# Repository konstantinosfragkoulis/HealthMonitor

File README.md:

# HealthMonitor 

Bare metal wearable for real-time Electrocardiogram (ECG), Seismocardiogram (SCG), and respiratory rate extraction.

**Core Stack:** STM32U5 (Cortex-M33) | ST1VAFE6AX (6-axis IMU) | AD8232 (ECG AFE)

## Architecture & DSP
To guarantee precise timing, the firmware relies entirely on hardware synchronization. The IMU's data-ready external interrupt triggers a simultaneous DMA transfer for both the SPI bus (IMU) and the ADC (ECG). This locks both data streams to a 480 Hz sample rate, eliminating software polling jitter.

The main loop runs three independent DSP pipelines on-device:

* **ECG (Pan-Tompkins++):** Bandpass -> derivative -> squaring -> flattop smoothing -> MWI. Uses adaptive thresholding with search-back for real-time R-peak detection [1].
* **SCG (Template Matching NCC):** Accel Z-axis (dorso-ventral) filtered at 7-30 Hz. Bootstraps a heartbeat template during the first 10s via a 4th-power envelope and pairwise NCC [2]. Runs a sliding normalized cross-correlation against the template for continuous AO detection. The template is double-buffered and refreshed every 60s.
* **Respiratory Rate:** Accel Z-axis LPF -> decimated 48:1 (to 10 Hz) -> bandpass 0.1-0.6 Hz. Fed into a 30-second autocorrelation window, outputting a new respiratory rate every 5 seconds.

HRV metrics (RMSSD, SDNN, pNN50, SD1, SD2) are calculated independently for both the ECG and SCG streams over a 60 second sliding window based on Task Force standards [3,4]. ECG and SCG reports are synchronized as the ECG trigger drives both computations simultaneously. Data is streamed to a host via a USB Virtual COM Port with CRC-32 integrity.

## Project Structure
* `/hardware/HM-Rev1`: First spin. **See `ERRATA.md`** (known routing/schematic flaw with the AD8232).
* `/hardware/HM-Rev2`: Fixed AD8232 layout, added USB-C, placed components on the bottom layer.
* `/fw`: STM32CubeIDE project, bare-metal C source, DSP logic, and TinyUSB stack.
* `/software`: Python telemetry parser and plotter.

## Roadmap
- [x] Hardware validation.
- [x] Synchronized IMU + ECG DMA capture.
- [x] ECG R-peak detection (Pan-Tompkins++).
- [x] SCG heartbeat detection (Template Matching NCC).
- [x] Real-time respiratory rate from chest-wall accelerometry.
- [x] On-device HRV metrics calculation.
- [x] USB CDC telemetry via TinyUSB.
- [x] SCG vs ECG HRV validation.
- [ ] Improve SCG RMSSD agreement
- [ ] Multi-axis respiratory fusion (PCA + gyro).

## SCG vs ECG HRV Validation

To validate the SCG pipeline, both streams are recorded simultaneously and HRV metrics are compared using Bland-Altman analysis, Pearson correlation, and ICC(2,1). Results from a 30 minute resting session (single subject, n=57 paired reports after 4 outliers removed via 3xIQR on RMSSD):

| Metric | Bias | 95% LOA | r | ICC(2,1) |
|--------|------|---------|---|----------|
| SDNN | -2.0 ms | [-6.0, +1.9] | 0.988 | 0.961 |
| SD2 | -0.9 ms | [-3.6, +1.9] | 0.996 | 0.994 |
| RMSSD | -6.3 ms | [-16.2, +3.5] | 0.378 | 0.175 |

SDNN and SD2 show excellent agreement. RMSSD underestimates ECG systematically. The SCG pipeline captures long term variability accurately but doesn't perform well with beat-to-beat variations.

The validation script reports both unfiltered and filtered results.
Run `python software/analyze.py <session_dir>` to produce the table and plots with data saved from the `software/monitor.py` script.

## Build Instructions
Compiled with **STM32CubeIDE**.
1. `git clone https://github.com/konstantinosfragkoulis/HealthMonitor.git`
2. Open STM32CubeIDE > `File > STM32 Project Create/Import > Import STM32 Project > STM32CubeMX/STM32CubeIDE Project`.
3. Point to the `/fw` directory.
4. Build (Release/Debug) and flash via ST-Link.

## Host Telemetry
The STM32 streams binary packets over USB CDC. Use the included Python script to plot sensor data in real time.

```bash
cd software
pip install pyserial numpy matplotlib # You might want to use a virtual environment for this

# Auto detect port
python monitor.py

# Manually select port
python monitor.py COM3         # Windows
python monitor.py /dev/ttyACM0 # Linux
```

## References
- USB stack powered by the open-source [TinyUSB](https://github.com/hathach/tinyusb) library (MIT License).

[1] M. N. Imtiaz and N. Khan, "Pan-Tompkins++: A Robust Approach to Detect R-peaks in ECG Signals," in *Proc. IEEE Int. Conf. Bioinformatics and Biomedicine (BIBM) Workshops*, 2022. [Online]. Available: https://arxiv.org/abs/2211.03171

[2] S. Parlato, J. Centracchio, D. Esposito, P. Bifulco, and E. Andreozzi, "Fully automated template matching method for ECG-free heartbeat detection in cardiomechanical signals," *Physical and Engineering Sciences in Medicine*, vol. 48, pp. 649-664, 2025.

[3] Task Force of the European Society of Cardiology and the North American Society of Pacing and Electrophysiology, "Heart rate variability: standards of measurement, physiological interpretation and clinical use," *Circulation*, vol. 93, pp. 1043-1065, 1996.

[4] F. Shaffer and J. P. Ginsberg, "An Overview of Heart Rate Variability Metrics and Norms," *Frontiers in Public Health*, vol. 5, 258, 2017.

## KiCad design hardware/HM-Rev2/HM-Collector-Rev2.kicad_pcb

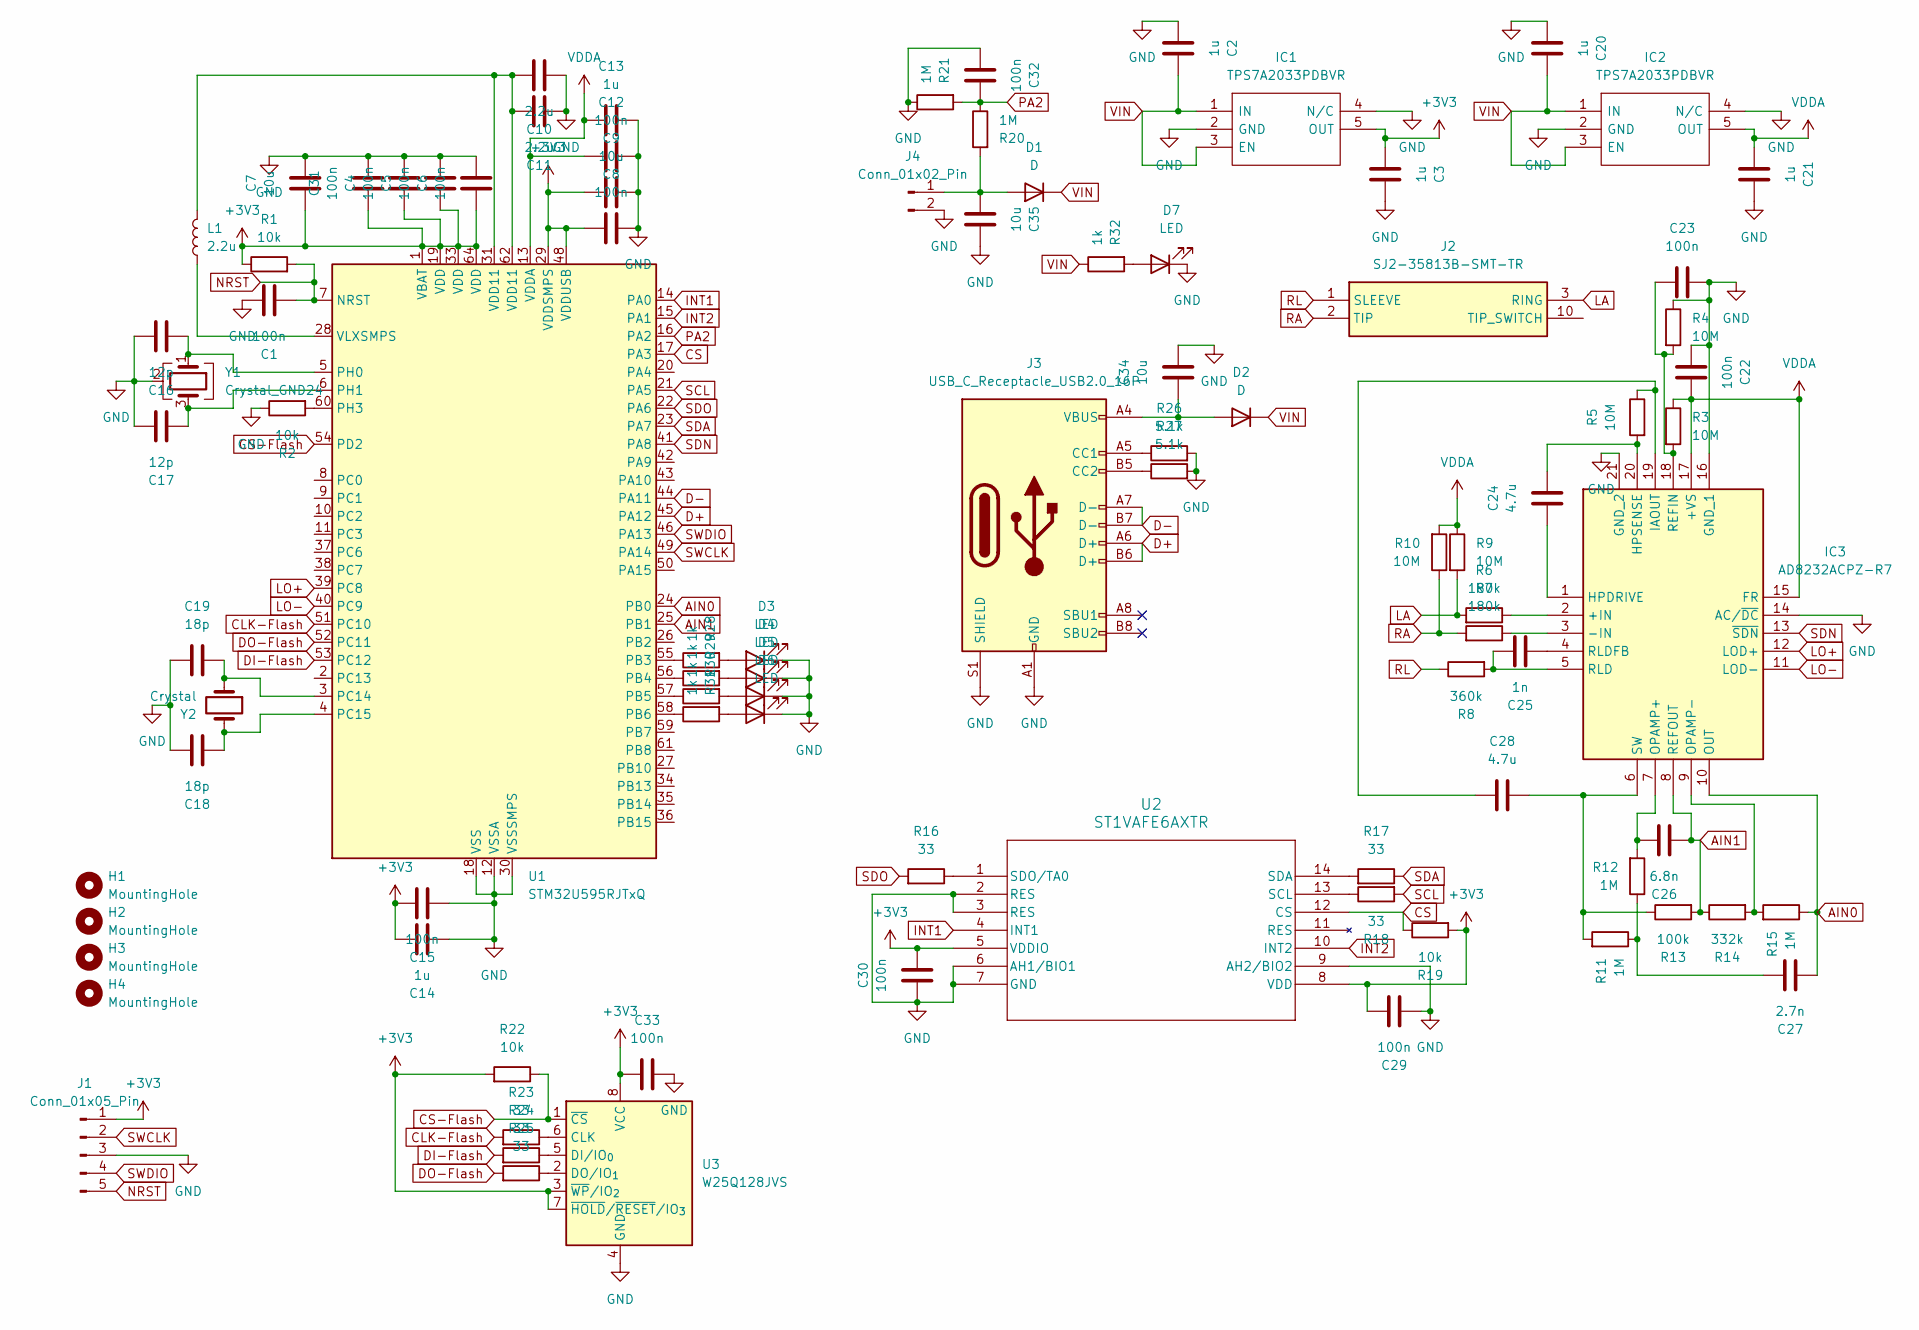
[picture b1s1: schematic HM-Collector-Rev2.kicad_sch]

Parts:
C1, C4, C5, C6, C8, C12, C15, C22, C23, C29, C30, C31, C32, C33: 100n; C_0603_1608Metric
C2, C3, C13, C14, C20, C21: 1u; C_0603_1608Metric
C7, C9, C34, C35: 10u; C_0805_2012Metric
C10, C11: 2.2u; C_0603_1608Metric
C16, C17: 12p; C_0402_1005Metric
C18, C19: 18p; C_0402_1005Metric
C24, C28: 4.7u; C_0805_2012Metric
C25: 1n; C_0603_1608Metric
C26: 6.8n; C_0402_1005Metric
C27: 2.7n; C_0603_1608Metric
D1, D2: D; D_SOD-123
D3, D4, D5, D6, D7: LED; LED_0603_1608Metric
H1, H2, H3, H4: MountingHole; MountingHole_2.2mm_M2
IC1, IC2: TPS7A2033PDBVR; SOT95P280X145-5N; Manufacturer_Part_Number TPS7A2033PDBVR; Mouser Part Number 595-TPS7A2033PDBVR
IC3: AD8232ACPZ-R7; QFN50P400X400X80-21N-D; Mouser Part Number 584-AD8232ACPZ-R7
J1: Conn_01x05_Pin; PinHeader_1x05_P2.54mm_Horizontal
J2: SJ2-35813B-SMT-TR; SJ235813BSMTTR; Mouser Part Number 490-SJ2-35813BSMT-TR
J3: USB_C_Receptacle_USB2.0_16P; USB_C_Receptacle_GCT_USB4105-xx-A_16P_TopMnt_Horizontal
J4: Conn_01x02_Pin; PinHeader_1x02_P2.54mm_Vertical
L1: 2.2u; L_1008_2520Metric
R1, R2, R19, R22: 10k; R_0603_1608Metric
R3, R4, R5, R9, R10: 10M; R_0603_1608Metric
R6, R7: 180k; R_0603_1608Metric
R8: 360k; R_0603_1608Metric
R11, R12, R15, R20, R21: 1M; R_0603_1608Metric
R13: 100k; R_0603_1608Metric
R14: 332k; R_0603_1608Metric
R16, R17, R18, R23, R24, R25: 33; R_0603_1608Metric
R26, R27: 5.1k; R_0603_1608Metric
R28, R29, R30, R31, R32: 1k; R_0603_1608Metric
U1: STM32U595RJTxQ; LQFP-64_10x10mm_P0.5mm
U2: ST1VAFE6AXTR; LGA-14L_STM
U3: W25Q128JVS; SOIC-8_5.3x5.3mm_P1.27mm
Y1: Crystal_GND24; Crystal_SMD_3225-4Pin_3.2x2.5mm
Y2: Crystal; Crystal_SMD_3215-2Pin_3.2x1.5mm

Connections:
+3V3: C3.2, C4.2, C5.2, C6.2, C7.2, C8.2, C9.2, C14.2, C15.1, C29.1, C30.1, C31.2, C33.2, IC1.5 (OUT), J1.1, R1.1, R19.2, R22.2, U1.1 (VBAT), U1.19 (VDD), U1.29 (VDDSMPS), U1.33 (VDD), U1.48 (VDDUSB), U1.64 (VDD), U2.5 (VDDIO), U2.8 (VDD), U3.3 (~WP/IO_{2}), U3.7 (~HOLD/~RESET/IO_{3}), U3.8 (VCC)
AIN0: C27.2, IC3.10 (OUT), R15.1, U1.24 (PB0)
AIN1: C26.2, IC3.8 (REFOUT), R13.2, R14.1, U1.25 (PB1)
CLK-Flash: R23.2, U1.51 (PC10)
CS: R19.1, U1.17 (PA3), U2.12 (CS)
CS-Flash: R22.1, U1.54 (PD2), U3.1 (~CS)
D+: J3.A6 (D+), J3.B6 (D+), U1.45 (PA12)
D-: J3.A7 (D-), J3.B7 (D-), U1.44 (PA11)
DI-Flash: R24.2, U1.53 (PC12)
DO-Flash: R25.2, U1.52 (PC11)
GND: C1.1, C2.2, C3.1, C4.1, C5.1, C6.1, C7.1, C8.1, C9.1, C10.1, C11.1, C12.1, C13.2, C14.1, C15.2, C16.1, C17.1, C18.1, C19.2, C20.2, C21.1, C22.2, C23.1, C29.2, C30.2, C31.1, C32.2, C33.1, C34.1, C35.1, D3.1 (K), D4.1 (K), D5.1 (K), D6.1 (K), D7.1 (K), IC1.2 (GND), IC1.4 (N/C), IC2.2 (GND), IC2.4 (N/C), IC3.14 (AC/~DC), IC3.16 (GND_1), IC3.21 (GND_2), J1.3, J3.A1 (GND), J3.A12 (GND), J3.B1 (GND), J3.B12 (GND), J3.S1 (SHIELD), J4.2, R2.1, R4.1, R21.1, R26.2, R27.2, U1.12 (VSSA), U1.18 (VSS), U1.30 (VSSSMPS), U1.32 (VSS), U1.47 (VSS), U1.63 (VSS), U2.2 (RES), U2.3 (RES), U2.6 (AH1/BIO1), U2.7 (GND), U2.9 (AH2/BIO2), U3.4 (GND), Y1.2 (G), Y1.4 (G)
INT1: U1.14 (PA0), U2.4 (INT1)
INT2: U1.15 (PA1), U2.10 (INT2)
LA: J2.3 (RING), R6.2, R9.2
LO+: IC3.12 (LOD+), U1.39 (PC8)
LO-: IC3.11 (LOD-), U1.40 (PC9)
NRST: C1.2, J1.5, R1.2, U1.7 (NRST)
unnamed: C10.2, C11.2, L1.2, U1.31 (VDD11), U1.62 (VDD11)
unnamed: C27.1, R11.1, R12.1
unnamed: C35.2, D1.2 (A), J4.1, R20.2
unnamed: C34.2, D2.2 (A), J3.A4 (VBUS), J3.A9 (VBUS), J3.B4 (VBUS), J3.B9 (VBUS)
unnamed: D3.2 (A), R28.2
unnamed: D4.2 (A), R29.2
unnamed: D5.2 (A), R30.2
unnamed: D6.2 (A), R31.2
unnamed: D7.2 (A), R32.2
unnamed: IC3.2 (+IN), R6.1
unnamed: IC3.3 (-IN), R7.1
unnamed: C24.2, IC3.1 (HPDRIVE)
unnamed: C24.1, IC3.20 (HPSENSE), R5.2
unnamed: C28.2, IC3.19 (IAOUT), R5.1
unnamed: C26.1, IC3.7 (OPAMP+), R12.2
unnamed: IC3.9 (OPAMP-), R14.2, R15.2
unnamed: C23.2, IC3.18 (REFIN), R3.2, R4.2
unnamed: C25.1, IC3.5 (RLD), R8.2
unnamed: C25.2, IC3.4 (RLDFB)
unnamed: C28.1, IC3.6 (SW), R11.2, R13.1
unnamed: J3.A5 (CC1), R26.1
unnamed: J3.B5 (CC2), R27.1
unnamed: R28.1, U1.55 (PB3)
unnamed: R29.1, U1.56 (PB4)
unnamed: R30.1, U1.57 (PB5)
unnamed: R31.1, U1.58 (PB6)
unnamed: C19.1, U1.3 (PC14), Y2.1
unnamed: C18.2, U1.4 (PC15), Y2.2
unnamed: C16.2, U1.5 (PH0), Y1.1
unnamed: C17.2, U1.6 (PH1), Y1.3
unnamed: R2.2, U1.60 (PH3)
unnamed: L1.1, U1.28 (VLXSMPS)
unnamed: R18.1, U2.13 (SCL)
unnamed: R17.2, U2.14 (SDA)
unnamed: R16.1, U2.1 (SDO/TA0)
unnamed: R23.1, U3.6 (CLK)
unnamed: R24.1, U3.5 (DI/IO_{0})
unnamed: R25.1, U3.2 (DO/IO_{1})
PA2: C32.1, R20.1, R21.2, U1.16 (PA2)
RA: J2.2 (TIP), R7.2, R10.1
RL: J2.1 (SLEEVE), R8.1
SCL: R18.2, U1.21 (PA5)
SDA: R17.1, U1.23 (PA7)
SDN: IC3.13 (~SDN), U1.41 (PA8)
SDO: R16.2, U1.22 (PA6)
SWCLK: J1.2, U1.49 (PA14)
SWDIO: J1.4, U1.46 (PA13)
VDDA: C12.2, C13.1, C21.2, C22.1, IC2.5 (OUT), IC3.15 (FR), IC3.17 (+VS), R3.1, R9.1, R10.2, U1.13 (VDDA)
VIN: C2.1, C20.1, D1.1 (K), D2.1 (K), IC1.1 (IN), IC1.3 (EN), IC2.1 (IN), IC2.3 (EN), R32.1

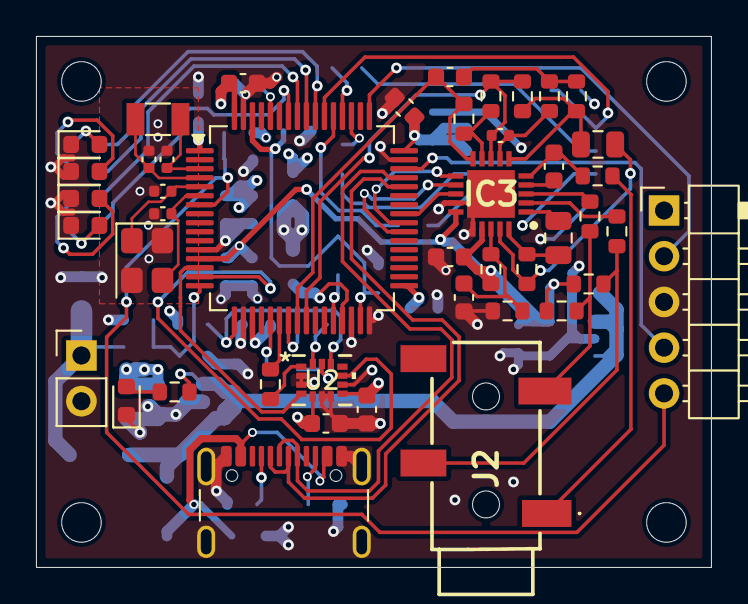
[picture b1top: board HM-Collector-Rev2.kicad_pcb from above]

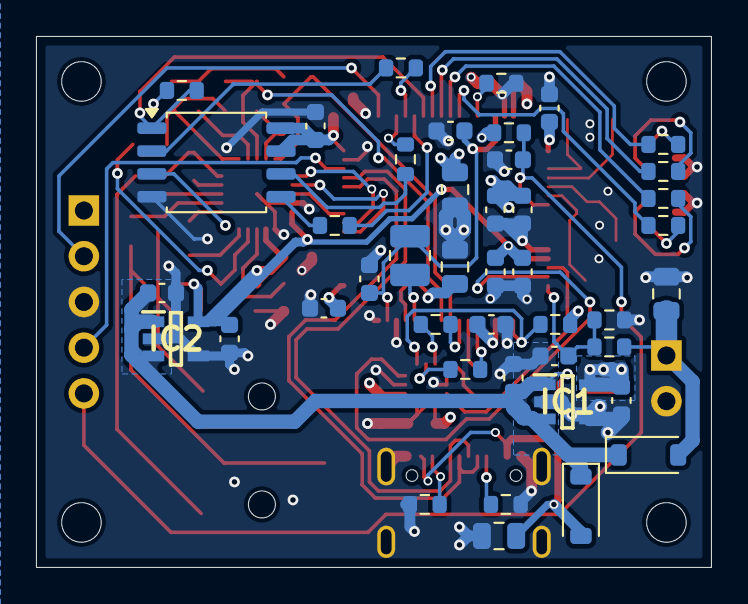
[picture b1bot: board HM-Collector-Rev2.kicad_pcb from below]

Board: 4 copper layers, 37.5 x 29.5 mm, 91 parts (43 on the bottom side), 66 nets.

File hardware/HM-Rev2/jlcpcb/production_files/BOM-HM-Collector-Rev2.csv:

Comment,Designator,Footprint,LCSC,Quantity
100k,R13,R_0603_1608Metric,C25803,1
100n,"C1,C12,C15,C22,C23,C29,C30,C31,C32,C33,C4,C5,C6,C8",C_0603_1608Metric,C14663,14
10M,"R10,R3,R4,R5,R9",R_0603_1608Metric,C7250,5
10k,"R1,R19,R2,R22",R_0603_1608Metric,C25804,4
10u,"C34,C35,C7,C9",C_0805_2012Metric,C440198,4
12p,"C16,C17",C_0402_1005Metric,C1547,2
180k,"R6,R7",R_0603_1608Metric,C22827,2
18p,"C18,C19",C_0402_1005Metric,C1549,2
1M,"R11,R12,R15,R20,R21",R_0603_1608Metric,C22935,5
1k,"R28,R29,R30,R31,R32",R_0603_1608Metric,C21190,5
1n,C25,C_0603_1608Metric,C1588,1
1u,"C13,C14,C2,C20,C21,C3",C_0603_1608Metric,C15849,6
2.2u,"C10,C11",C_0603_1608Metric,C23630,2
2.7n,C27,C_0603_1608Metric,C1609,1
33,"R16,R17,R18,R23,R24,R25",R_0603_1608Metric,C23140,6
4.7u,"C24,C28",C_0805_2012Metric,C1779,2
5.1k,"R26,R27",R_0603_1608Metric,C23186,2
6.8n,C26,C_0402_1005Metric,C1542,1
AD8232ACPZ-R7,IC2,QFN50P400X400X80-21N-D,C43216,1
Crystal,Y2,Crystal_SMD_3215-2Pin_3.2x1.5mm,C32346,1
Crystal_GND24,Y1,Crystal_SMD_3225-4Pin_3.2x2.5mm,C13738,1
D,"D1,D2",D_SOD-123,C8598,2
LED,"D3,D5,D7",LED_0603_1608Metric,C2286,3
LED,"D4,D6",LED_0603_1608Metric,C2290,2
ST1VAFE6AXTR,U2,LGA-14L_STM,C23536654,1
STM32U595RJTxQ,U1,LQFP-64_10x10mm_P0.5mm,C27526235,1
TPS7A2028PDBVR,"IC1,IC3",SOT95P280X145-5N,C2862740,2
USB_C_Receptacle_USB2.0_16P,J3,USB_C_Receptacle_GCT_USB4105-xx-A_16P_TopMnt_Horizontal,C709357,1

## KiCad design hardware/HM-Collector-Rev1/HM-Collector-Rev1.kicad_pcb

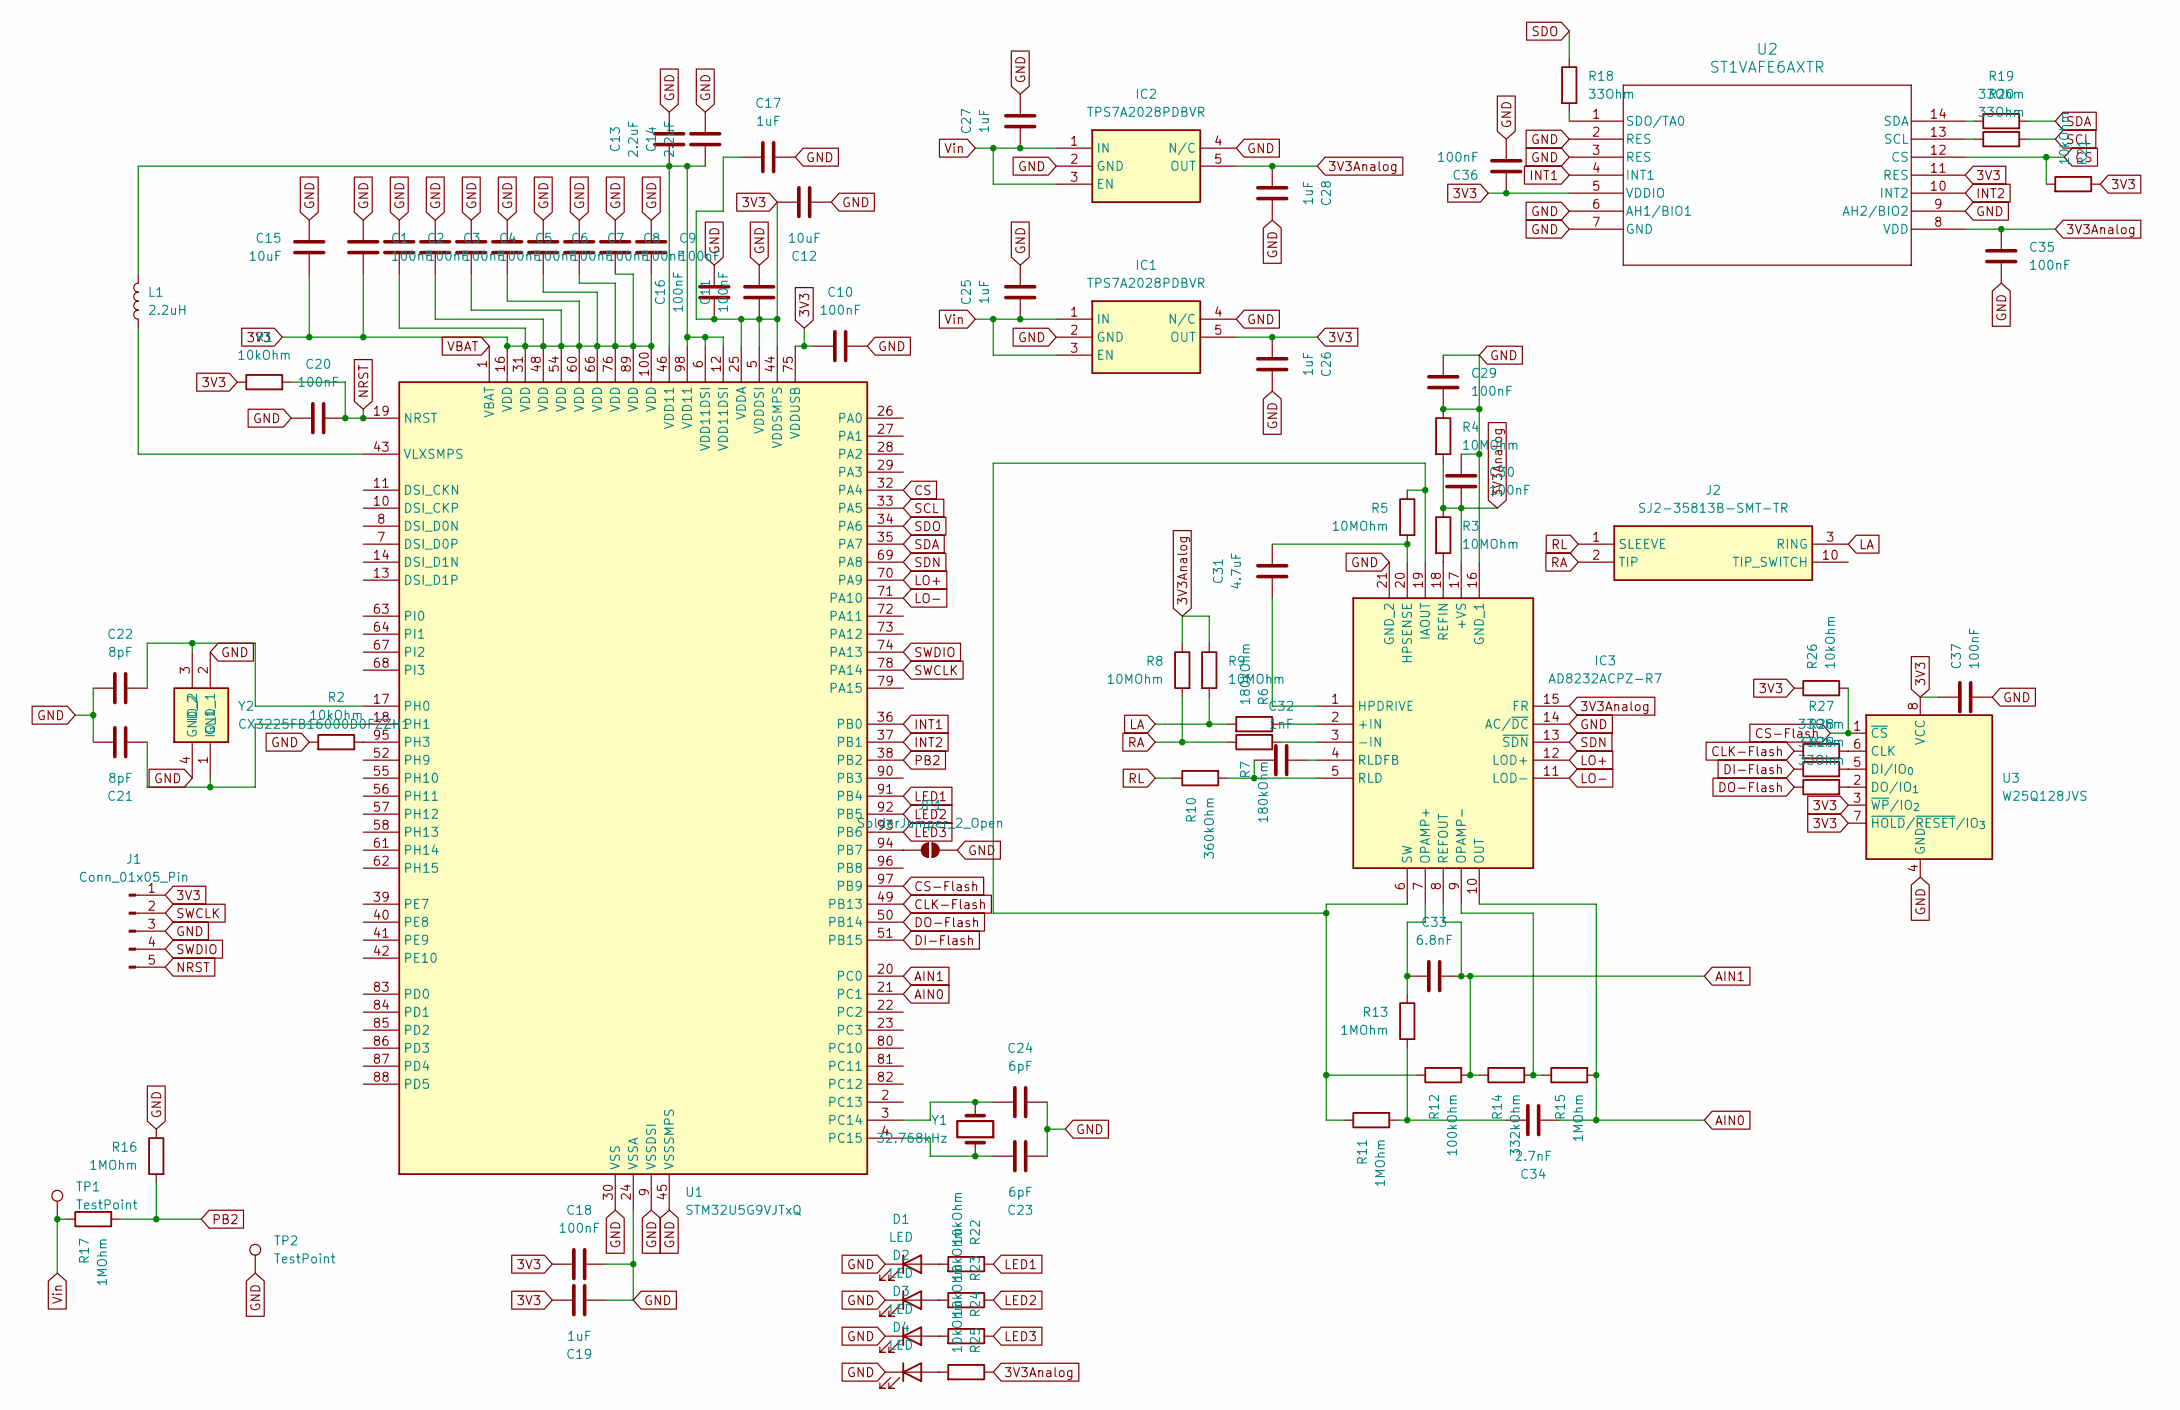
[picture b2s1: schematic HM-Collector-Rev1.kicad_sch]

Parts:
C1, C2, C3, C4, C5, C6, C7, C8, C9, C10, C11, C16, C18, C20, C29, C30, C35, C36, C37: 100nF; C_0603_1608Metric
C12, C15: 10uF; C_0805_2012Metric
C13, C14: 2.2uF; C_0603_1608Metric
C17, C19, C25, C26, C27, C28: 1uF; C_0603_1608Metric
C21, C22: 8pF; C_0402_1005Metric
C23, C24: 6pF; C_0402_1005Metric
C31: 4.7uF; C_0805_2012Metric
C32: 1nF; C_0603_1608Metric
C33: 6.8nF; C_0402_1005Metric
C34: 2.7nF; C_0402_1005Metric
D1, D2, D3, D4: LED; LED_0402_1005Metric_Pad0.77x0.64mm_HandSolder
IC1, IC2: TPS7A2028PDBVR; SOT95P280X145-5N; Mouser Part Number 595-TPS7A2028PDBVR
IC3: AD8232ACPZ-R7; QFN50P400X400X80-21N-D; Mouser Part Number 584-AD8232ACPZ-R7
J1: Conn_01x05_Pin; PinHeader_1x05_P2.54mm_Horizontal
J2: SJ2-35813B-SMT-TR; SJ235813BSMTTR; Mouser Part Number 490-SJ2-35813BSMT-TR
JP1: SolderJumper_2_Open; SolderJumper-2_P1.3mm_Open_Pad1.0x1.5mm
L1: 2.2uH; L_1008_2520Metric
R1, R2, R21, R22, R23, R24, R25, R26: 10kOhm; R_0603_1608Metric
R3, R4, R5, R8, R9: 10MOhm; R_0603_1608Metric
R6, R7: 180kOhm; R_0603_1608Metric
R10: 360kOhm; R_0603_1608Metric
R11, R13, R15, R16, R17: 1MOhm; R_0603_1608Metric
R12: 100kOhm; R_0603_1608Metric
R14: 332kOhm; R_0603_1608Metric
R18, R19, R20, R27, R28, R29: 33Ohm; R_0402_1005Metric
TP1, TP2: TestPoint; PinHeader_1x01_P2.54mm_Vertical
U1: STM32U5G9VJTxQ; LQFP-100_14x14mm_P0.5mm
U2: ST1VAFE6AXTR; LGA-14L_STM
U3: W25Q128JVS; SOIC-8_5.3x5.3mm_P1.27mm
Y1: 32.768kHz; Crystal_SMD_3215-2Pin_3.2x1.5mm
Y2: CX3225FB16000D0FZZH1; Manufacturer_Part_Number CX3225FB16000D0FZZH1

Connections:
3V3: C1.2, C2.2, C3.2, C4.2, C5.2, C6.2, C7.2, C8.2, C9.2, C10.1, C11.1, C12.1, C15.2, C16.1, C17.1, C18.2, C19.1, C26.1, C36.1, C37.1, IC1.5 (OUT), J1.1, R1.1, R21.1, R26.1, U1.5 (VDDDSI), U1.16 (VDD), U1.25 (VDDA), U1.31 (VDD), U1.44 (VDDSMPS), U1.48 (VDD), U1.54 (VDD), U1.60 (VDD), U1.66 (VDD), U1.75 (VDDUSB), U1.76 (VDD), U1.89 (VDD), U1.100 (VDD), U2.5 (VDDIO), U2.11 (RES), U3.3 (~WP/IO_{2}), U3.7 (~HOLD/~RESET/IO_{3}), U3.8 (VCC)
3V3Analog: C28.1, C30.1, C35.1, IC2.5 (OUT), IC3.15 (FR), IC3.17 (+VS), R3.1, R4.2, R8.1, R9.1, R25.1, U2.8 (VDD)
AIN0: C34.2, IC3.10 (OUT), R15.2, U1.21 (PC1)
AIN1: C33.1, IC3.8 (REFOUT), R12.2, R14.1, U1.20 (PC0)
CLK-Flash: R27.1, U1.49 (PB13)
CS: R21.2, U1.32 (PA4), U2.12 (CS)
CS-Flash: R26.2, U1.97 (PB9), U3.1 (~CS)
DI-Flash: R28.1, U1.51 (PB15)
DO-Flash: R29.1, U1.50 (PB14)
GND: C1.1, C2.1, C3.1, C4.1, C5.1, C6.1, C7.1, C8.1, C9.1, C10.2, C11.2, C12.2, C13.2, C14.2, C15.1, C16.2, C17.2, C18.1, C19.2, C20.1, C21.1, C22.2, C23.2, C24.1, C25.2, C26.2, C27.2, C28.2, C29.1, C29.2, C30.2, C35.2, C36.2, C37.2, D1.1 (K), D2.1 (K), D3.1 (K), D4.1 (K), IC1.2 (GND), IC1.4 (N/C), IC2.2 (GND), IC2.4 (N/C), IC3.14 (AC/~DC), IC3.16 (GND_1), IC3.21 (GND_2), J1.3, JP1.2 (B), R2.2, R4.1, R16.1, TP2.1, U1.9 (VSSDSI), U1.15 (VSSDSI), U1.24 (VSSA), U1.30 (VSS), U1.45 (VSSSMPS), U1.47 (VSS), U1.53 (VSS), U1.59 (VSS), U1.65 (VSS), U1.77 (VSS), U1.99 (VSS), U2.2 (RES), U2.3 (RES), U2.6 (AH1/BIO1), U2.7 (GND), U2.9 (AH2/BIO2), U3.4 (GND), Y2.2 (GND_1), Y2.4 (GND_2)
INT1: U1.36 (PB0), U2.4 (INT1)
INT2: U1.37 (PB1), U2.10 (INT2)
LA: J2.3 (RING), R6.2, R9.2
LED1: R22.1, U1.91 (PB4)
LED2: R23.1, U1.92 (PB5)
LED3: R24.1, U1.93 (PB6)
LO+: IC3.12 (LOD+), U1.70 (PA9)
LO-: IC3.11 (LOD-), U1.71 (PA10)
NRST: C20.2, J1.5, R1.2, U1.19 (NRST)
unnamed: C13.1, C14.1, L1.2, U1.6 (VDD11DSI), U1.12 (VDD11DSI), U1.46 (VDD11), U1.98 (VDD11)
unnamed: C34.1, R11.2, R13.2
unnamed: D1.2 (A), R22.2
unnamed: D2.2 (A), R23.2
unnamed: D3.2 (A), R24.2
unnamed: D4.2 (A), R25.2
unnamed: IC3.2 (+IN), R6.1
unnamed: IC3.3 (-IN), R7.2
unnamed: C31.1, IC3.1 (HPDRIVE)
unnamed: C31.2, IC3.20 (HPSENSE), R5.2
unnamed: IC3.6 (SW), IC3.19 (IAOUT), R5.1, R11.1, R12.1
unnamed: C33.2, IC3.7 (OPAMP+), R13.1
unnamed: IC3.9 (OPAMP-), R14.2, R15.1
unnamed: IC3.18 (REFIN), R3.2
unnamed: C32.2, IC3.5 (RLD), R10.2
unnamed: C32.1, IC3.4 (RLDFB)
unnamed: JP1.1 (A), U1.94 (PB7)
unnamed: C24.2, U1.3 (PC14), Y1.2
unnamed: C23.1, U1.4 (PC15), Y1.1
unnamed: C22.1, U1.17 (PH0), Y2.3 (IO_2)
unnamed: C21.2, U1.18 (PH1), Y2.1 (IO_1)
unnamed: R2.1, U1.95 (PH3)
unnamed: L1.1, U1.43 (VLXSMPS)
unnamed: R20.1, U2.13 (SCL)
unnamed: R19.1, U2.14 (SDA)
unnamed: R18.2, U2.1 (SDO/TA0)
unnamed: R27.2, U3.6 (CLK)
unnamed: R28.2, U3.5 (DI/IO_{0})
unnamed: R29.2, U3.2 (DO/IO_{1})
PB2: R16.2, R17.2, U1.38 (PB2)
RA: J2.2 (TIP), R7.1, R8.2
RL: J2.1 (SLEEVE), R10.1
SCL: R20.2, U1.33 (PA5)
SDA: R19.2, U1.35 (PA7)
SDN: IC3.13 (~SDN), U1.69 (PA8)
SDO: R18.1, U1.34 (PA6)
SWCLK: J1.2, U1.78 (PA14)
SWDIO: J1.4, U1.74 (PA13)
VBAT: U1.1 (VBAT)
Vin: C25.1, C27.1, IC1.1 (IN), IC1.3 (EN), IC2.1 (IN), IC2.3 (EN), R17.1, TP1.1

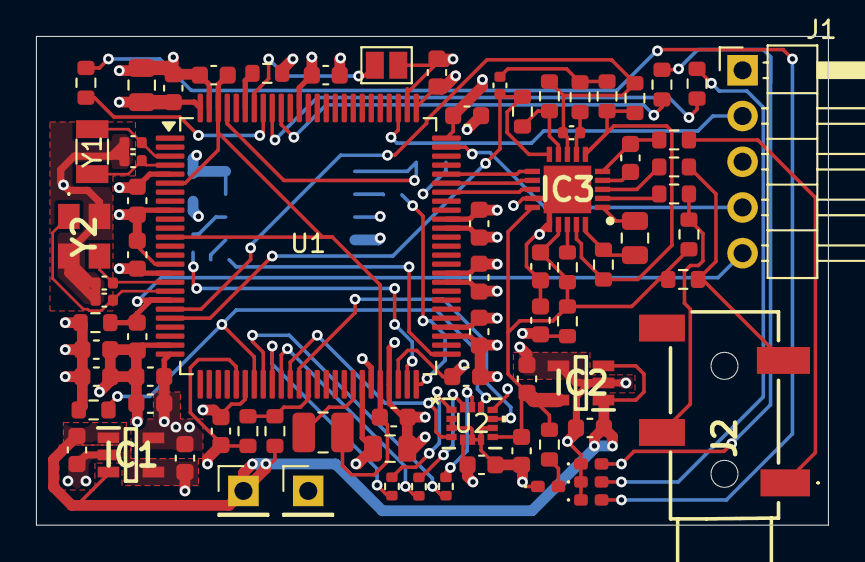
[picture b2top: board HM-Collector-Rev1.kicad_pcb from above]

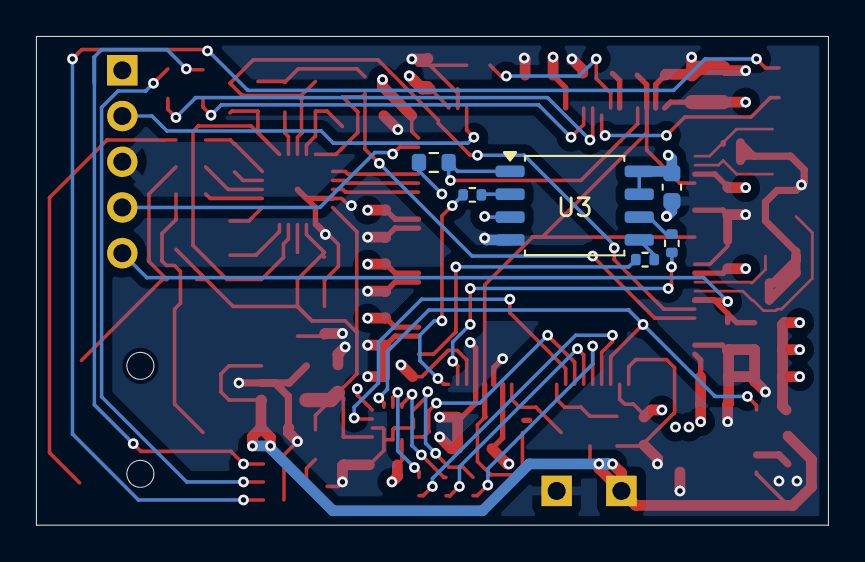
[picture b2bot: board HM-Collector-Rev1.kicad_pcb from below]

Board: 4 copper layers, 44.0 x 27.2 mm, 84 parts (6 on the bottom side), 58 nets.

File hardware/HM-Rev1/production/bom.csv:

Designator,Footprint,Quantity,Value,LCSC Part #
"C1, C10, C11, C16, C18, C2, C20, C29, C3, C30, C35, C36, C37, C4, C5, C6, C7, C8, C9",0603,19,100nF,
"C12, C15",0805,2,10uF,
"C13, C14",0603,2,2.2uF,
"C17, C19, C25, C26, C27, C28",0603,6,1uF,
"C21, C22",0402,2,8pF,
"C23, C24",0402,2,6pF,
C31,0805,1,4.7uF,
C32,0603,1,1nF,
C33,0402,1,6.8nF,
C34,0402,1,2.7nF,
"D1, D2, D3, D4",0402,4,LED,
"IC1, IC2",SOT95P280X145-5N,2,TPS7A2028PDBVR,
IC3,QFN50P400X400X80-21N-D,1,AD8232ACPZ-R7,
J1,PinHeader_1x05_P2.54mm_Horizontal,1,Conn_01x05_Pin,
J2,SJ235813BSMTTR,1,SJ2-35813B-SMT-TR,
L1,1008,1,2.2uH,
"R1, R2, R21, R22, R23, R24, R25, R26",0603,8,10kOhm,
R10,0603,1,360kOhm,
"R11, R13, R15, R16, R17",0603,5,1MOhm,
R12,0603,1,100kOhm,
R14,0603,1,332kOhm,
"R18, R19, R20, R27, R28, R29",0402,6,33Ohm,
"R3, R4, R5, R8, R9",0603,5,10MOhm,
"R6, R7",0603,2,180kOhm,
"TP1, TP2",PinHeader_1x01_P2.54mm_Vertical,2,TestPoint,
U1,LQFP-100_14x14mm_P0.5mm,1,STM32U5G9VJTxQ,
U2,LGA-14L_STM,1,ST1VAFE6AXTR,
U3,SOIC-8_5.3x5.3mm_P1.27mm,1,W25Q128JVS,
Y1,Crystal_SMD_3215-2Pin_3.2x1.5mm,1,32.768kHz,
Y2,CX3225FB16000D0FZZH1,1,CX3225FB16000D0FZZH1,

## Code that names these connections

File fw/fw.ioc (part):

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Mcu.Name=STM32U595RJTxQ
Mcu.Package=LQFP64
Mcu.UserName=STM32U595RJTxQ
PA0.GPIOParameters=GPIO_Label
PA0.GPIO_Label=IMU_INT1
PA0.Signal=GPXTI0
PA1.GPIOParameters=GPIO_Label
PA1.GPIO_Label=IMU_INT2
PA1.Signal=GPXTI1
PA11.Mode=Internal_Phy_Device
PA11.Signal=USB_OTG_HS_DM
PA12.Mode=Internal_Phy_Device
PA12.Signal=USB_OTG_HS_DP
PA13\ (JTMS/SWDIO).Mode=Serial_Wire
PA13\ (JTMS/SWDIO).Signal=DEBUG_JTMS-SWDIO
PA14\ (JTCK/SWCLK).Mode=Serial_Wire
PA14\ (JTCK/SWCLK).Signal=DEBUG_JTCK-SWCLK
PA2.Mode=IN7-Single-Ended
PA2.Signal=ADC1_IN7
PA3.GPIOParameters=GPIO_Speed,PinState,GPIO_Label,GPIO_ModeDefaultOutputPP
PA3.GPIO_Label=IMU_CS
PA3.GPIO_ModeDefaultOutputPP=GPIO_MODE_OUTPUT_PP
PA3.GPIO_Speed=GPIO_SPEED_FREQ_LOW
PA3.PinState=GPIO_PIN_SET
PA3.Signal=GPIO_Output
PA5.Mode=Full_Duplex_Master
PA5.Signal=SPI1_SCK
PA6.GPIOParameters=GPIO_PuPd
PA6.GPIO_PuPd=GPIO_NOPULL
PA6.Mode=Full_Duplex_Master
PA6.Signal=SPI1_MISO
PA7.Mode=Full_Duplex_Master
PA7.Signal=SPI1_MOSI
PA8.GPIOParameters=PinState,GPIO_Label
PA8.GPIO_Label=ECG_SDN
PA8.PinState=GPIO_PIN_SET
PA8.Signal=GPIO_Output
PB0.Mode=IN15-Single-Ended
PB0.Signal=ADC1_IN15
PB1.Mode=IN16-Single-Ended
PB1.Signal=ADC1_IN16
PB3\ (JTDO/TRACESWO).GPIOParameters=GPIO_Label
PB3\ (JTDO/TRACESWO).GPIO_Label=LED_1
PB3\ (JTDO/TRACESWO).Signal=GPIO_Output
PB4\ (NJTRST).GPIOParameters=GPIO_Label
PB4\ (NJTRST).GPIO_Label=LED_2
PB4\ (NJTRST).Signal=GPIO_Output
PB5.GPIOParameters=GPIO_Label
PB5.GPIO_Label=LED_3
PB5.Signal=GPIO_Output
PB6.GPIOParameters=GPIO_Label
PB6.GPIO_Label=LED_4
PB6.Signal=GPIO_Output
PC10.Mode=Full_Duplex_Master
PC10.Signal=SPI3_SCK
PC11.Mode=Full_Duplex_Master
PC11.Signal=SPI3_MISO
PC12.Mode=Full_Duplex_Master
PC12.Signal=SPI3_MOSI
PC14-OSC32_IN\ (PC14).Mode=LSE-External-Oscillator
PC14-OSC32_IN\ (PC14).Signal=RCC_OSC32_IN
PC15-OSC32_OUT\ (PC15).Mode=LSE-External-Oscillator
PC15-OSC32_OUT\ (PC15).Signal=RCC_OSC32_OUT
PC8.GPIOParameters=GPIO_Label
PC8.GPIO_Label=ECG_LOP
PC8.Signal=GPIO_Input
PC9.GPIOParameters=GPIO_Label
PC9.GPIO_Label=ECG_LON
PC9.Signal=GPIO_Input
PD2.GPIOParameters=GPIO_Speed,PinState,GPIO_Label
PD2.GPIO_Label=Flash_CS
PD2.GPIO_Speed=GPIO_SPEED_FREQ_VERY_HIGH
PD2.PinState=GPIO_PIN_SET
PD2.Signal=GPIO_Output
PH0-OSC_IN\ (PH0).Mode=HSE-External-Oscillator
PH0-OSC_IN\ (PH0).Signal=RCC_OSC_IN
PH1-OSC_OUT\ (PH1).Mode=HSE-External-Oscillator
PH1-OSC_OUT\ (PH1).Signal=RCC_OSC_OUT
RCC.HSE_VALUE=16000000
RCC.SYSCLKFreq_VALUE=160000000
RCC.SYSCLKSource=RCC_SYSCLKSOURCE_PLLCLK
board=custom

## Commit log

2025-12-23 Ignore everything
2025-12-23 Collector Rev1 design
2026-03-01 Rev2 design files
2026-03-01 Fix image path in README.md
    Updated image path for the Health Monitor PCB.
2026-03-05 Add the MIT license
2026-03-07 Don't ignore BOM files
2026-03-07 Rename Rev1 directory and add documentation/production files
2026-03-28 Initial ECG and IMU firmware
2026-03-29 Fixed whoami check
2026-03-30 Project files for CubeIDE
2026-03-30 Fix PT++ implementation
2026-04-02 Implemented IMU DSP pipeline
2026-04-02 Refactor beat processing, fix SDNN divisor, zero reserved bytes
2026-04-09 Fix SCG refractory bug, cap template NCC peaks, increase FIFO sizes
2026-04-09 cleanup
2026-04-09 Add CSV data logging, fix duplicate packets
2026-04-16 Use 60s window for HRV metrics, fix SDNN divisor
2026-04-16 Synchronize ECG and SCG HRV reports
2026-04-16 Fix SCG template refresh
2026-04-16 Increase sensor FIFO size
2026-04-16 Add HRV validation script
2026-04-16 Add SCG vs ECG HRV validation
2026-04-16 Refactor/cleanup
